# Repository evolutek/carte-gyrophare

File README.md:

# carte-gyrophare
Carte pour contrôler la rotation du miroir du gryrophare et pour l'arrêt d'urgence

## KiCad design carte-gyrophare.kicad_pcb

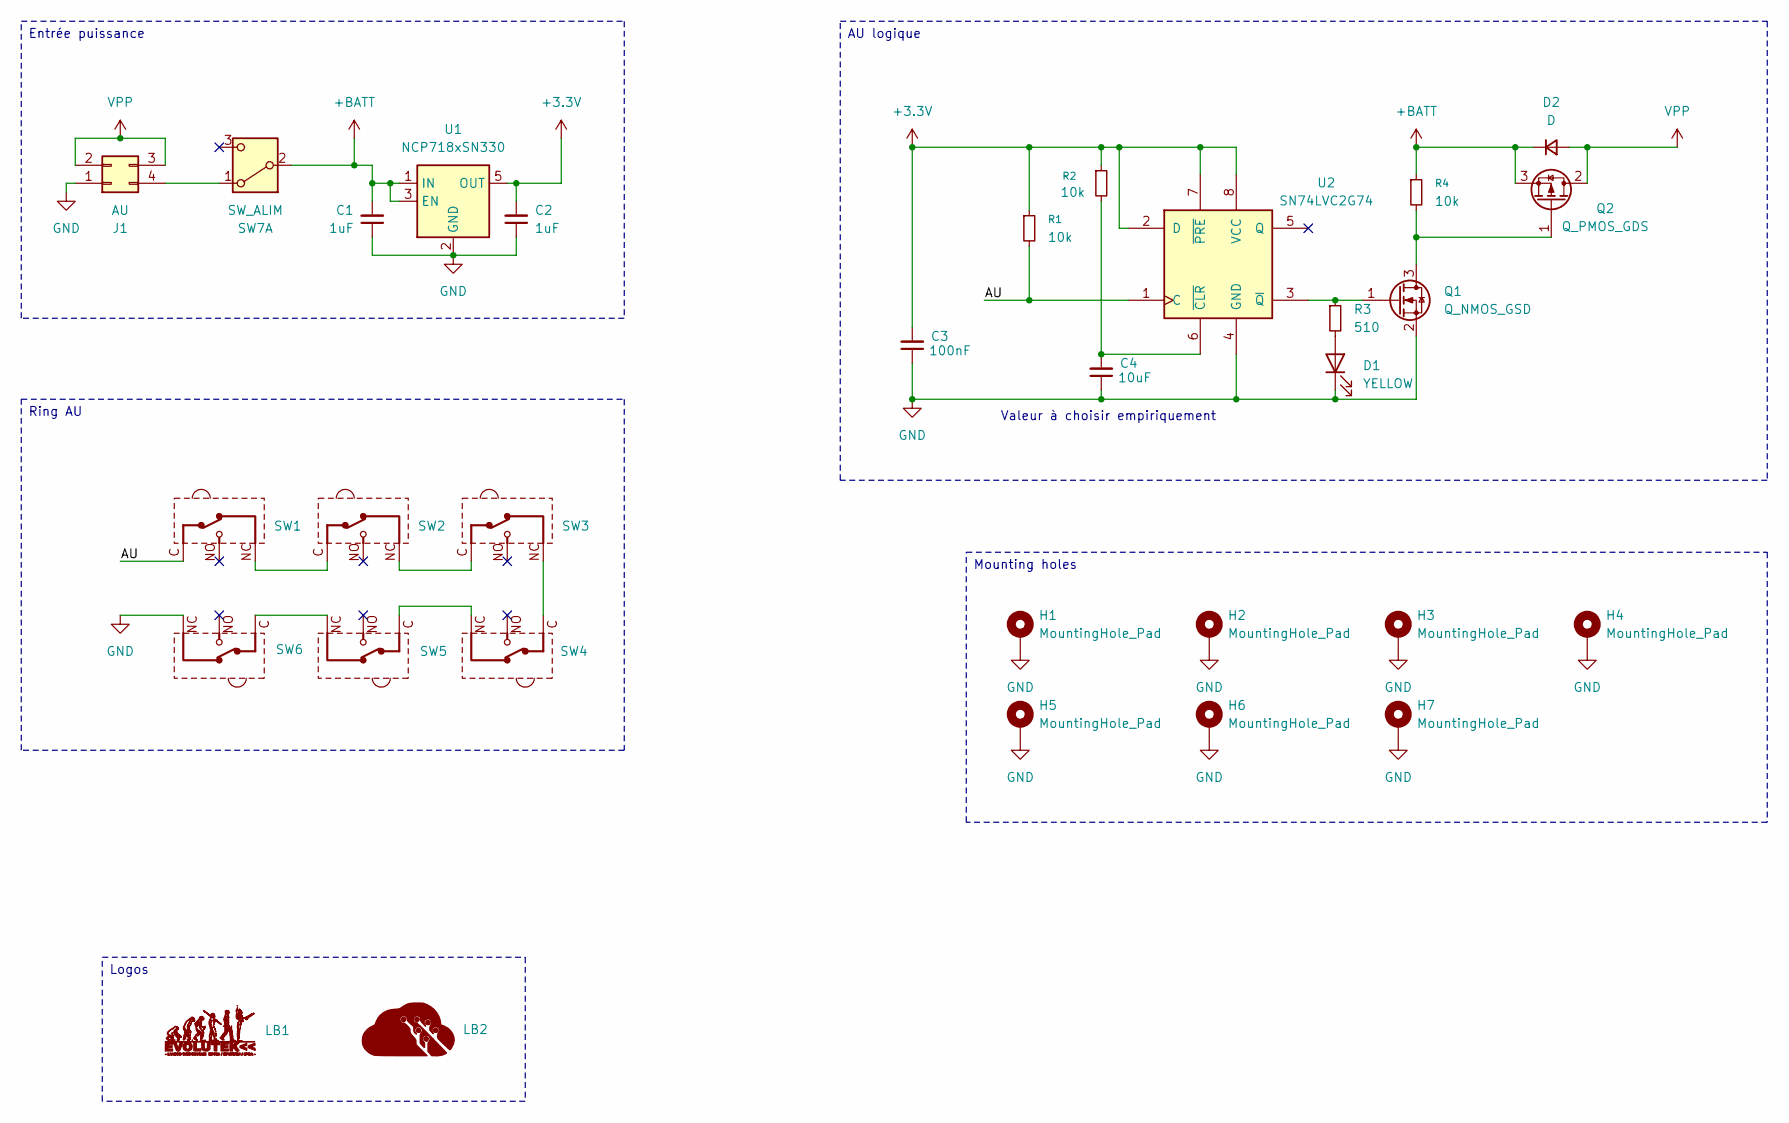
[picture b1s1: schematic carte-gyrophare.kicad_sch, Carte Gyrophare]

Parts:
C1, C2: 1uF; C_0603_1608Metric
C3: 100nF; C_0603_1608Metric
C4: 10uF; CP_Radial_D10.0mm_P5.00mm
D1: YELLOW; LED_0805_2012Metric
D2: D; D_SMB
H1, H2, H3, H4, H5, H6, H7: MountingHole_Pad; MountingHole_3.2mm_M3_Pad_Via
J1: AU; 66200421122
LB1: LOGO; logo-evo-min
LB2: LOGO; Logo Aisler Min
Q1: Q_NMOS_GSD; SOT-23
Q2: Q_PMOS_GDS; SOT-223-3_TabPin2
R1, R2, R4: 10k; R_0603_1608Metric
R3: 510; R_0603_1608Metric
SW1, SW2, SW3, SW4, SW5, SW6: 463092370402
SW7: SW_ALIM; Power Switch RS SPDT Angled
U1: NCP718xSN330; SOT-23-5
U2: SN74LVC2G74; VSSOP-8_2.3x2mm_P0.5mm

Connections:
+3.3V: C2.2, C3.2, R1.1, R2.1, U1.5 (OUT), U2.2 (D), U2.7 (~PRE), U2.8 (VCC)
+BATT: C1.2, D2.1 (K), Q2.3 (S), R4.1, SW7.2 (B), U1.1 (IN), U1.3 (EN)
/AU: R1.2, SW1.1 (C), U2.1 (C)
GND: C1.1, C2.1, C3.1, C4.1, D1.1 (K), H1.1, H2.1, H3.1, H4.1, H5.1, H6.1, H7.1, J1.1, Q1.2 (S), SW6.3 (C), U1.2 (GND), U2.4 (GND)
unnamed: D1.2 (A), R3.2
unnamed: J1.4, SW7.1 (A)
unnamed: Q1.3 (D), Q2.1 (G), R4.2
unnamed: Q1.1 (G), R3.1, U2.3 (~Q)
unnamed: SW1.3 (C), SW2.1 (C)
unnamed: SW2.3 (C), SW3.1 (C)
unnamed: SW3.3 (C), SW4.1 (C)
unnamed: SW4.3 (C), SW5.1 (C)
unnamed: SW5.3 (C), SW6.1 (C)
unnamed: C4.2, R2.2, U2.6 (~CLR)
VPP: D2.2 (A), J1.2, J1.3, Q2.2 (D)

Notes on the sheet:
Valeur à choisir empiriquement
AU logique
Logos
Mounting holes
Entrée puissance
Ring AU

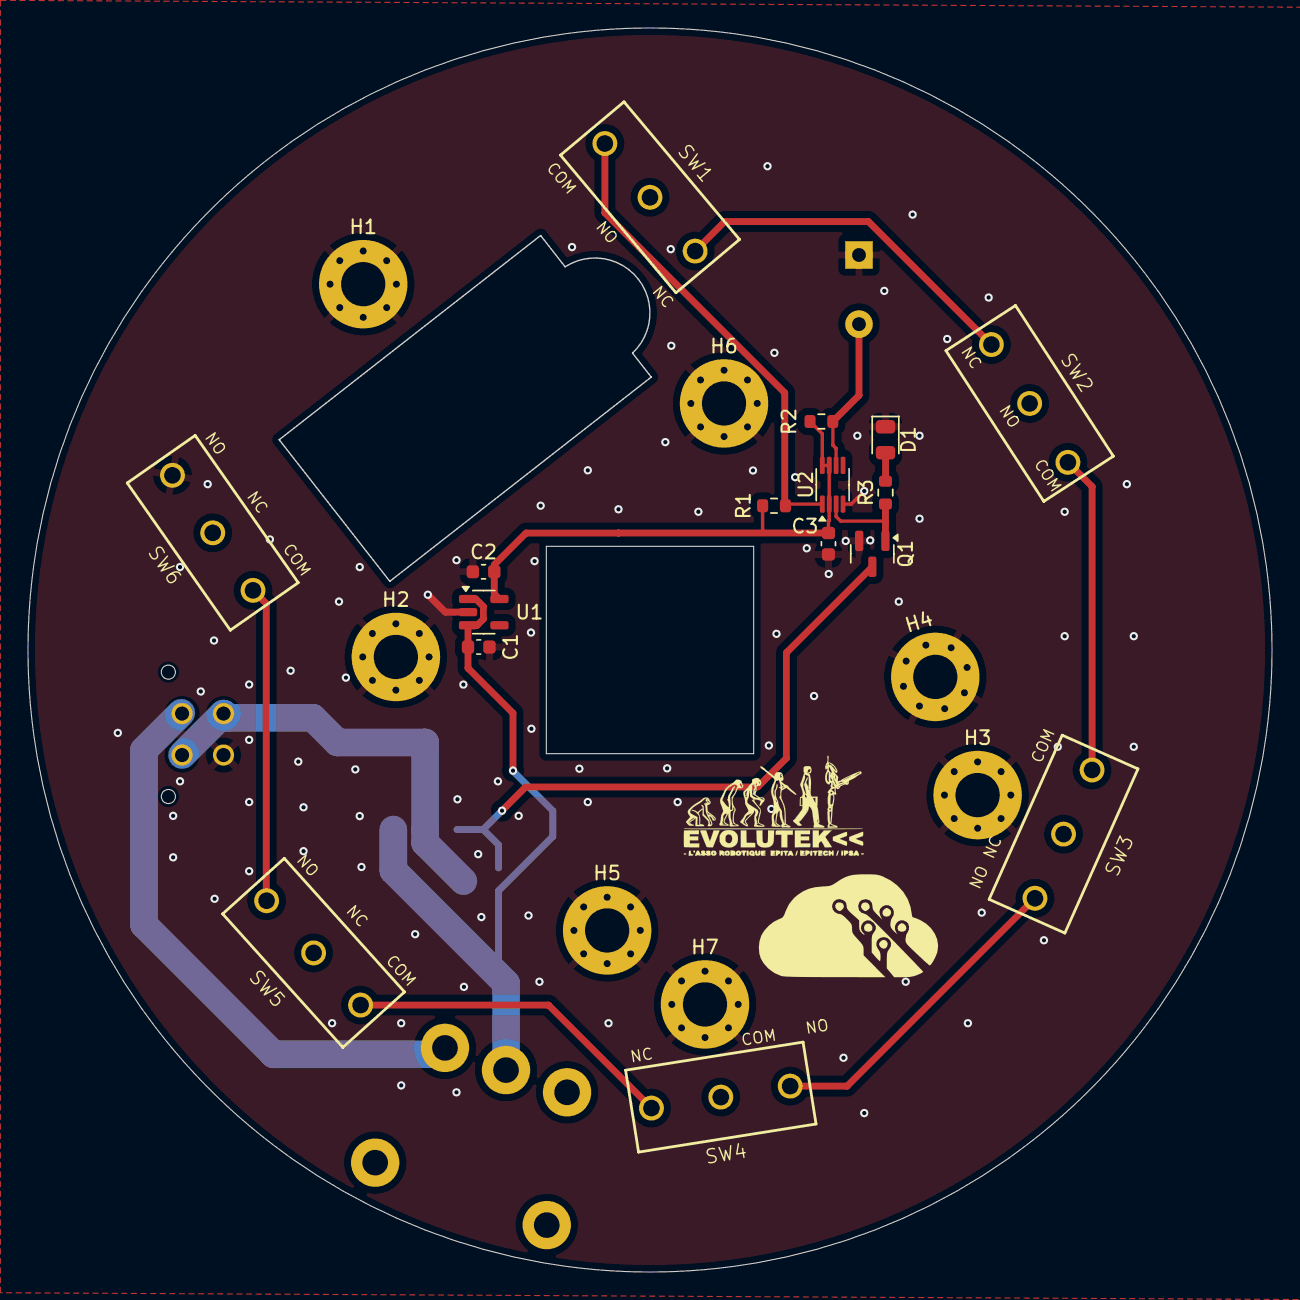
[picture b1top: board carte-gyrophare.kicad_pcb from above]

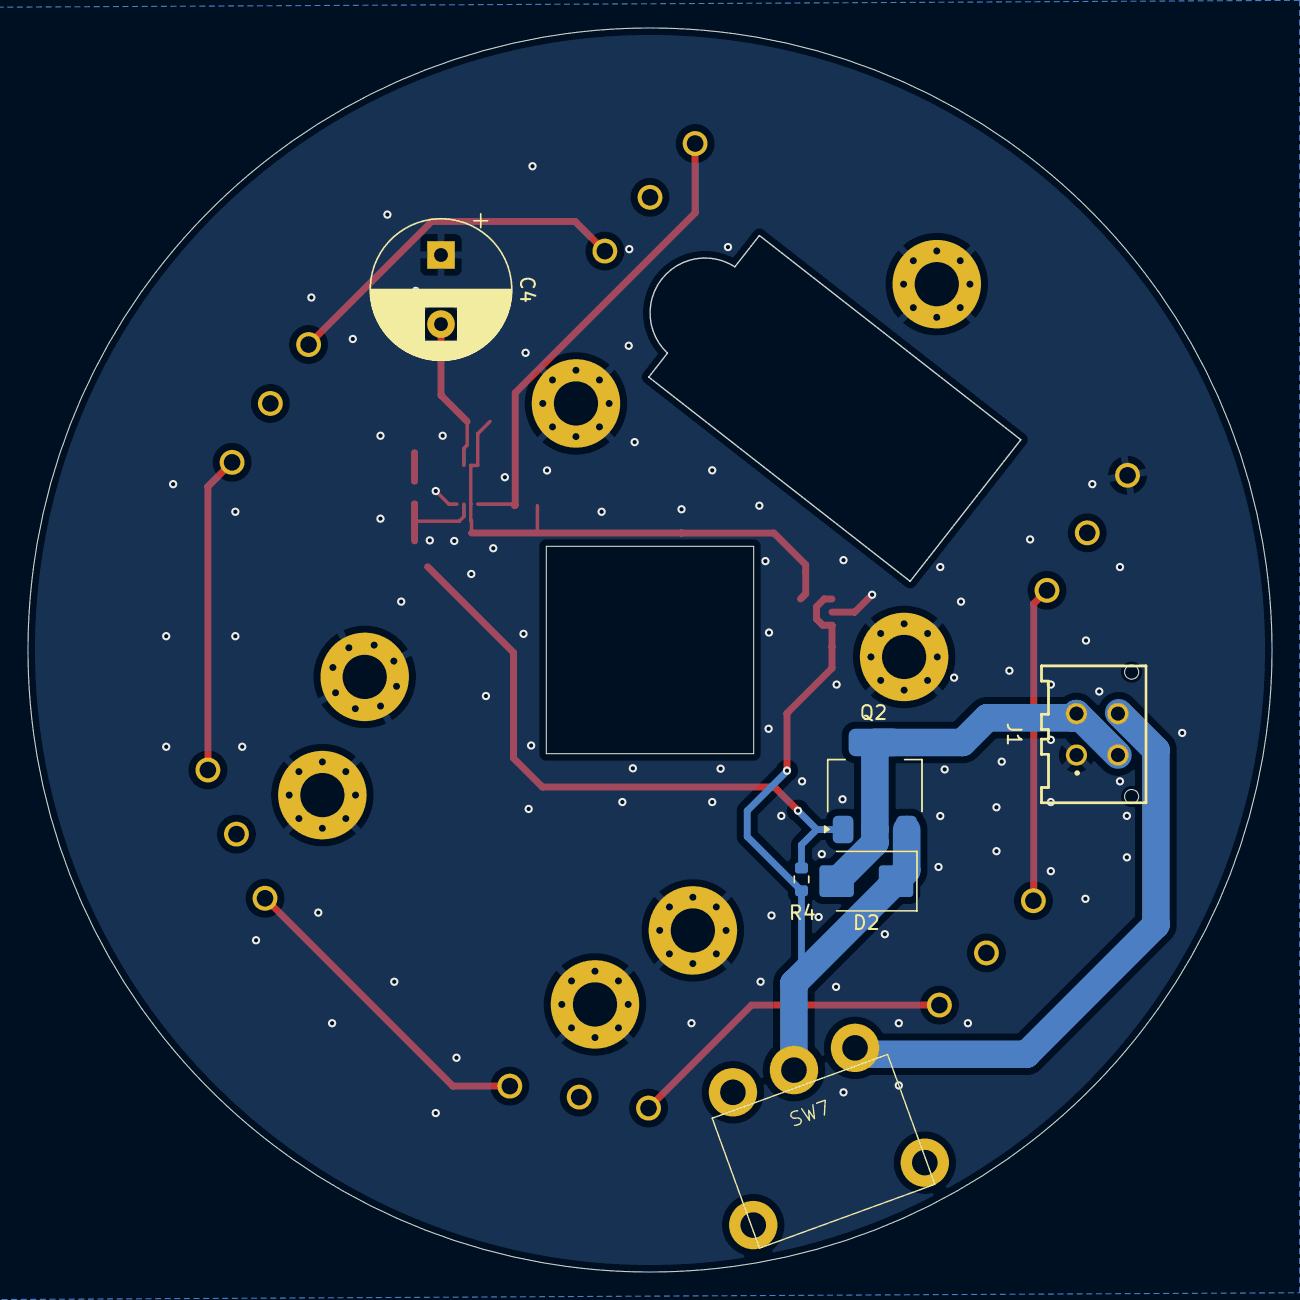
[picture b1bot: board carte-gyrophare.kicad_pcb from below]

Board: 2 copper layers, 90.0 x 90.0 mm, 31 parts (6 on the bottom side), 15 nets.

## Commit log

2025-04-30 feat: ma jolie carte
2025-05-05 cleanup
2025-05-07 fix: clean arborescence
2025-05-07 feat: add fixation holes
2025-05-07 feat: clean vias
2025-05-09 fix: resolve DRC issues
2025-05-09 fix: capa on back face
2025-05-09 fix: add autosaved and tmp files to gitignore
2025-05-09 feat: step
2025-05-09 fix: add hole for servo cables
2025-05-09 fix: rotate push button around servo
2025-05-09 fix: bigger hole for LED
2025-05-14 Release V1.0
2025-05-14 Clean repo
2025-05-21 Update BOM values
2025-05-21 Move to root folder
